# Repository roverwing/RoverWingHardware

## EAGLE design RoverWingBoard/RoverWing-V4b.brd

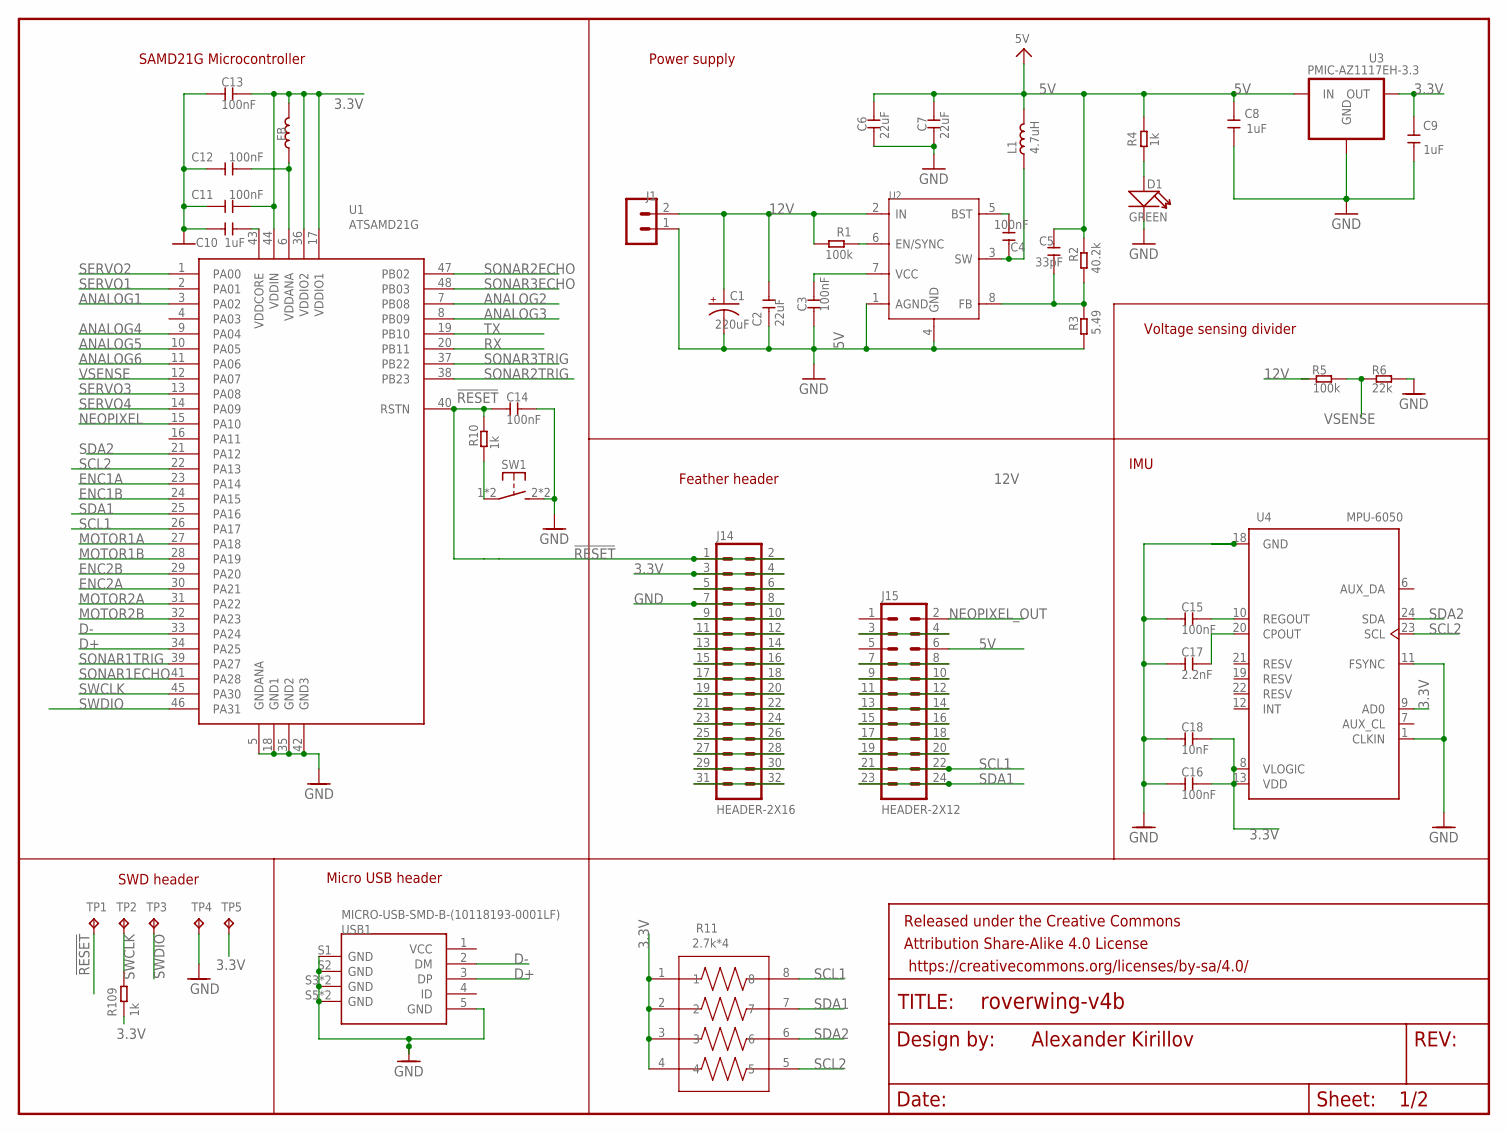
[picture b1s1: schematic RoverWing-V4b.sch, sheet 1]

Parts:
C1: 220uF; CAP-8X10.5
C2, C6, C7: 22uF; 0805
C3, C4, C11, C12, C13, C14, C15, C16: 100nF; 0805
C5: 33pF; 0805
C8, C9, C10: 1uF; 0805
C17: 2.2nF; 0805
C18: 10nF; 0805
D1: GREEN; LED-0805
FB: 330R-1500MA; 0805
FRAME2: FRAME-LETTERNO_PACKAGE; DUMMY
J1: HEADER-VH; B2P-VH
J14: HEADER-2X16; 2X16
J15: HEADER-2X12; 2X12
L1: 4.7uH; IND_TDK_7.1X6.5
R1, R5: 100k; 0805
R2: 40.2k; 0805
R3: 5.49; 0805
R4, R10, R109: 1k; 0805
R6: 22k; 0805
R11: 2.7k*4; 0603*4
SW1: SW-TACTILE-4.5X4.5_SMD; TL3305
TP1, TP2, TP3, TP4, TP5: TPTP15R; TP15R
U1: ATSAMD21G; TQFP-48-EDITED
U2: PMIC-MP2225; SOT-23-8
U3: PMIC-AZ1117EH-3.3; SOT223
U4: MPU-6050; QFN50P400X400X95-24N
USB1: MICRO-USB-SMD-B-(10118193-0001LF); MICRO-USB5+6P-SMD-0.65-B

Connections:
3.3V: C9.2, C11.2, C13.2, C16.2, C18.2, FB.2, J14.3, J14.4, R11.1, R11.2, R11.3, R11.4, R109.1, TP5.TP, U1.17 (VDDIO1), U1.36 (VDDIO2), U1.44 (VDDIN), U3.2 (OUT), U3.4 (OUT), U4.8 (VLOGIC), U4.9 (AD0), U4.13 (VDD); also elsewhere on the board
5V: C5.2, C6.2, C7.2, C8.2, J15.6, L1.2, R2.1, R4.2, U3.3 (IN); also elsewhere on the board
12V: C1.+, C2.2, J1.2, R1.2, R5.2, U2.2 (IN); also elsewhere on the board
!RESET: C14.1, J14.1, J14.2, R10.2, TP1.TP, U1.40 (RSTN)
ANALOG1: U1.3 (PA02); also elsewhere on the board
ANALOG2: U1.7 (PB08); also elsewhere on the board
ANALOG3: U1.8 (PB09); also elsewhere on the board
ANALOG4: U1.9 (PA04); also elsewhere on the board
ANALOG5: U1.10 (PA05); also elsewhere on the board
ANALOG6: U1.11 (PA06); also elsewhere on the board
BST: C4.1, U2.5 (BST)
D+: U1.34 (PA25), USB1.3 (DP)
D-: U1.33 (PA24), USB1.2 (DM)
ENC1A: U1.23 (PA14); also elsewhere on the board
ENC1B: U1.24 (PA15); also elsewhere on the board
ENC2A: U1.30 (PA21); also elsewhere on the board
ENC2B: U1.29 (PA20); also elsewhere on the board
FB: C5.1, R2.2, R3.1, U2.8 (FB)
GND: C1.-, C2.1, C3.1, C6.1, C7.1, C8.1, C9.1, C10.1, C11.1, C12.1, C13.1, C14.2, C15.1, C16.1, C17.1, C18.1, D1.-, J1.1, J14.7, J14.8, R3.2, R6.2, SW1.2 (S1), SW1.3 (S1), TP4.TP, U1.5 (GNDANA), U1.18 (GND1), U1.35 (GND2), U1.42 (GND3), U2.1 (AGND), U2.4 (GND), U3.1 (GND), U4.1 (CLKIN), U4.11 (FSYNC), U4.18 (GND), USB1.5 (GND), USB1.S1 (GND), USB1.S2 (GND), USB1.S3 (GND), USB1.S4 (GND), USB1.S5 (GND), USB1.S6 (GND); also elsewhere on the board
MOTOR1A: U1.27 (PA18); also elsewhere on the board
MOTOR1B: U1.28 (PA19); also elsewhere on the board
MOTOR2A: U1.31 (PA22); also elsewhere on the board
MOTOR2B: U1.32 (PA23); also elsewhere on the board
unnamed: C17.2, U4.20 (CPOUT)
unnamed: J15.3, J15.4
unnamed: C15.2, U4.10 (REGOUT)
unnamed: J15.7, J15.8
unnamed: R10.1, SW1.1, SW1.4 (P1)
unnamed: J15.9, J15.10
unnamed: C10.2, U1.43 (VDDCORE)
unnamed: J15.11, J15.12
unnamed: D1.+, R4.1
unnamed: J15.15, J15.16
unnamed: J15.13, J15.14
unnamed: R1.1, U2.6 (EN/SYNC)
unnamed: C3.2, U2.7 (VCC)
unnamed: J14.5, J14.6
unnamed: J15.17, J15.18
unnamed: J15.19, J15.20
unnamed: J14.9, J14.10
unnamed: J14.11, J14.12
unnamed: J14.13, J14.14
unnamed: J14.15, J14.16
unnamed: J14.17, J14.18
unnamed: J14.19, J14.20
unnamed: J14.21, J14.22
unnamed: J14.23, J14.24
unnamed: J14.25, J14.26
unnamed: J14.27, J14.28
unnamed: J14.29, J14.30
unnamed: J14.31, J14.32
NEOPIXEL: U1.15 (PA10); also elsewhere on the board
NEOPIXEL_OUT: J15.2; also elsewhere on the board
RX: U1.20 (PB11); also elsewhere on the board
SCL1: J15.21, J15.22, R11.8, U1.26 (PA17); also elsewhere on the board
SCL2: R11.5, U1.22 (PA13), U4.23 (SCL); also elsewhere on the board
SDA1: J15.23, J15.24, R11.7, U1.25 (PA16); also elsewhere on the board
SDA2: R11.6, U1.21 (PA12), U4.24 (SDA); also elsewhere on the board
SERVO1: U1.2 (PA01); also elsewhere on the board
SERVO2: U1.1 (PA00); also elsewhere on the board
SERVO3: U1.13 (PA08); also elsewhere on the board
SERVO4: U1.14 (PA09); also elsewhere on the board
SONAR1ECHO: U1.41 (PA28); also elsewhere on the board
SONAR1TRIG: U1.39 (PA27); also elsewhere on the board
SONAR2ECHO: U1.47 (PB02); also elsewhere on the board
SONAR2TRIG: U1.38 (PB23); also elsewhere on the board
SONAR3ECHO: U1.48 (PB03); also elsewhere on the board
SONAR3TRIG: U1.37 (PB22); also elsewhere on the board
SW: C4.2, L1.1, U2.3 (SW)
SWCLK: R109.2, TP2.TP, U1.45 (PA30)
SWDIO: TP3.TP, U1.46 (PA31)
TX: U1.19 (PB10); also elsewhere on the board
VDDANA: C12.2, FB.1, U1.6 (VDDANA)
VSENSE: R5.1, R6.1, U1.12 (PA07)

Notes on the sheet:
SWD header
Alexander Kirillov
SAMD21G Microcontroller
Micro USB header
Power supply
Feather header
IMU
Voltage sensing divider

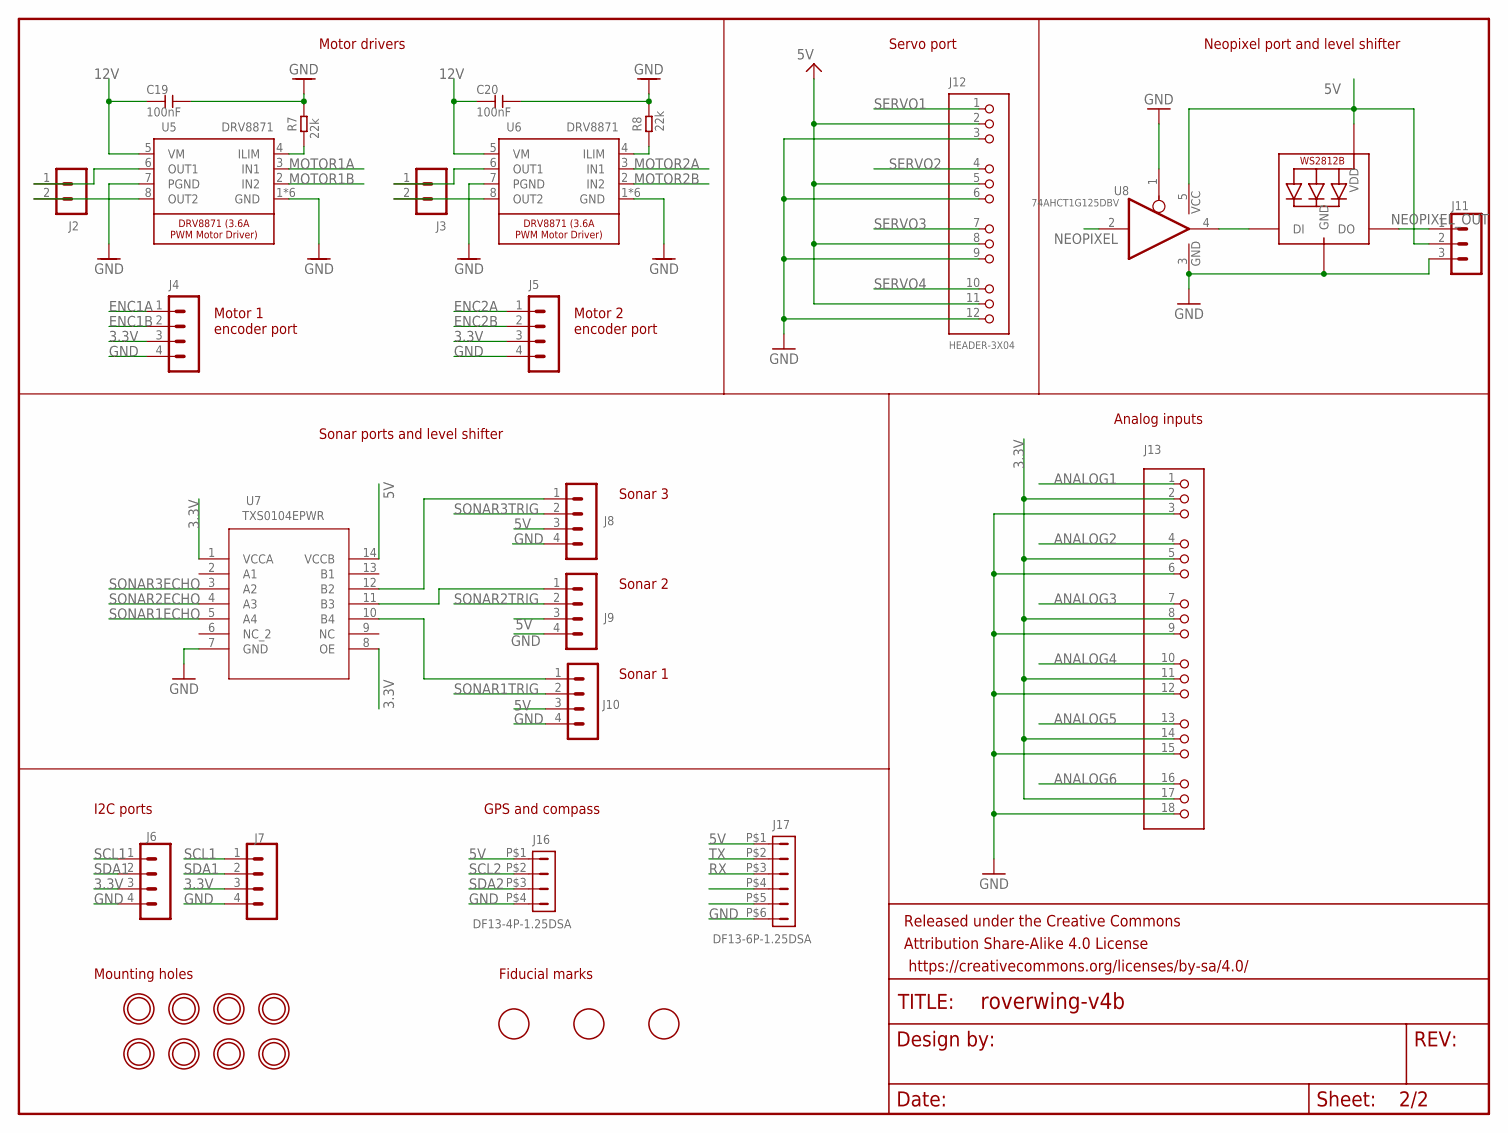
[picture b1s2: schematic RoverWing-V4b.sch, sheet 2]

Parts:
C19, C20: 100nF; 0805
FRAME1: FRAME-LETTERNO_PACKAGE; DUMMY
J2, J3: HEADER-VH; B2P-VH
J4, J5, J6, J7, J8, J9, J10: HEADER-PH-4P; B4B-PH-K
J11: HEADER-PH-3P; B3B-PH-K
J12: HEADER-3X04; 3X04
J13: HEADER-3X06"; 3X06
J16: DF13-4P-1.25DSA
J17: DF13-6P-1.25DSA
LED1: WS2812B3535; LED3535
R7, R8: 22k; 0805
U5, U6: DRV8871; HSOP8
U7: TXS0104EPWR; PW14
U8: 74AHCT1G125DBV; SOT23-5
U$3, U$4, U$14, U$15, U$24, U$25, U$26, U$27: MOUNTINGHOLE3.0_NPH; MOUNTINGHOLE_3.0_NPH
U$11, U$13, U$17: FIDUCIAL; FIDUCIAL_1MM

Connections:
3.3V: J4.3, J5.3, J6.3, J7.3, J13.2, J13.5, J13.8, J13.11, J13.14, J13.17, U7.1 (VCCA), U7.8 (OE); also elsewhere on the board
5V: J8.3, J9.3, J10.3, J11.2, J12.2, J12.5, J12.8, J12.11, J16.P$1 (1), J17.P$1 (1), LED1.2 (VDD), U7.14 (VCCB), U8.5 (VCC); also elsewhere on the board
12V: C19.1, C20.1, U5.5 (VM), U6.5 (VM); also elsewhere on the board
ANALOG1: J13.1; also elsewhere on the board
ANALOG2: J13.4; also elsewhere on the board
ANALOG3: J13.7; also elsewhere on the board
ANALOG4: J13.10; also elsewhere on the board
ANALOG5: J13.13; also elsewhere on the board
ANALOG6: J13.16; also elsewhere on the board
ENC1A: J4.1; also elsewhere on the board
ENC1B: J4.2; also elsewhere on the board
ENC2A: J5.1; also elsewhere on the board
ENC2B: J5.2; also elsewhere on the board
GND: C19.2, C20.2, J4.4, J5.4, J6.4, J7.4, J8.4, J9.4, J10.4, J11.3, J12.3, J12.6, J12.9, J12.12, J13.3, J13.6, J13.9, J13.12, J13.15, J13.18, J16.P$4 (4), J17.P$6 (6), LED1.4 (GND), R7.2, R8.2, U5.1 (GND), U5.7 (PGND), U5.GND, U5.P$1 (GND), U5.P$2 (GND), U5.P$3 (GND), U5.P$4 (GND), U6.1 (GND), U6.7 (PGND), U6.GND, U6.P$1 (GND), U6.P$2 (GND), U6.P$3 (GND), U6.P$4 (GND), U7.7 (GND), U8.1 (OE), U8.3 (GND); also elsewhere on the board
MOTOR1A: U5.3 (IN1); also elsewhere on the board
MOTOR1B: U5.2 (IN2); also elsewhere on the board
MOTOR2A: U6.3 (IN1); also elsewhere on the board
MOTOR2B: U6.2 (IN2); also elsewhere on the board
unnamed: J3.2, U6.8 (OUT2)
unnamed: J3.1, U6.6 (OUT1)
unnamed: J2.2, U5.8 (OUT2)
unnamed: J10.1, U7.10 (B4)
unnamed: J8.1, U7.12 (B2)
unnamed: J2.1, U5.6 (OUT1)
unnamed: R7.1, U5.4 (ILIM)
unnamed: R8.1, U6.4 (ILIM)
unnamed: J9.1, U7.11 (B3)
unnamed: LED1.1 (DI), U8.4 (O)
NEOPIXEL: U8.2 (I); also elsewhere on the board
NEOPIXEL_OUT: J11.1, LED1.3 (DO); also elsewhere on the board
RX: J17.P$3 (3); also elsewhere on the board
SCL1: J6.1, J7.1; also elsewhere on the board
SCL2: J16.P$2 (2); also elsewhere on the board
SDA1: J6.2, J7.2; also elsewhere on the board
SDA2: J16.P$3 (3); also elsewhere on the board
SERVO1: J12.1; also elsewhere on the board
SERVO2: J12.4; also elsewhere on the board
SERVO3: J12.7; also elsewhere on the board
SERVO4: J12.10; also elsewhere on the board
SONAR1ECHO: U7.5 (A4); also elsewhere on the board
SONAR1TRIG: J10.2; also elsewhere on the board
SONAR2ECHO: U7.4 (A3); also elsewhere on the board
SONAR2TRIG: J9.2; also elsewhere on the board
SONAR3ECHO: U7.3 (A2); also elsewhere on the board
SONAR3TRIG: J8.2; also elsewhere on the board
TX: J17.P$2 (2); also elsewhere on the board

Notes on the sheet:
Motor drivers
Motor 2 encoder port
Motor 1 encoder port
Sonar ports and level shifter
Analog inputs
Neopixel port and level shifter
Servo port
Sonar 3
Sonar 2
Sonar 1
Mounting holes
Fiducial marks
I2C ports
GPS and compass

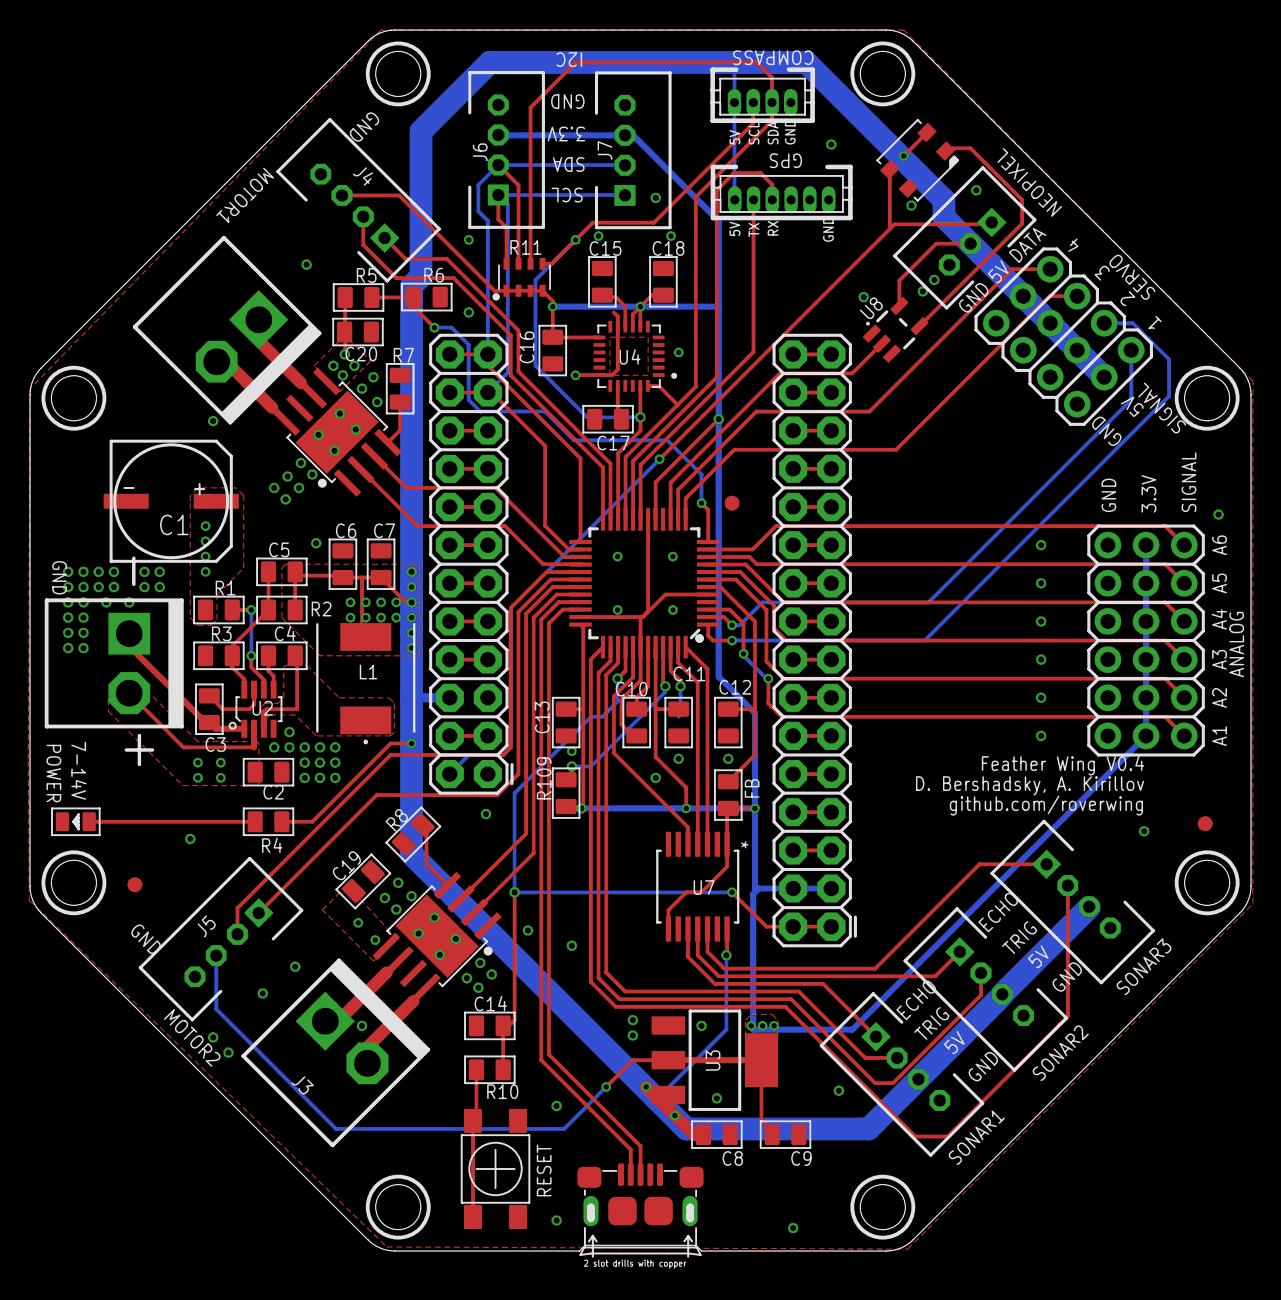
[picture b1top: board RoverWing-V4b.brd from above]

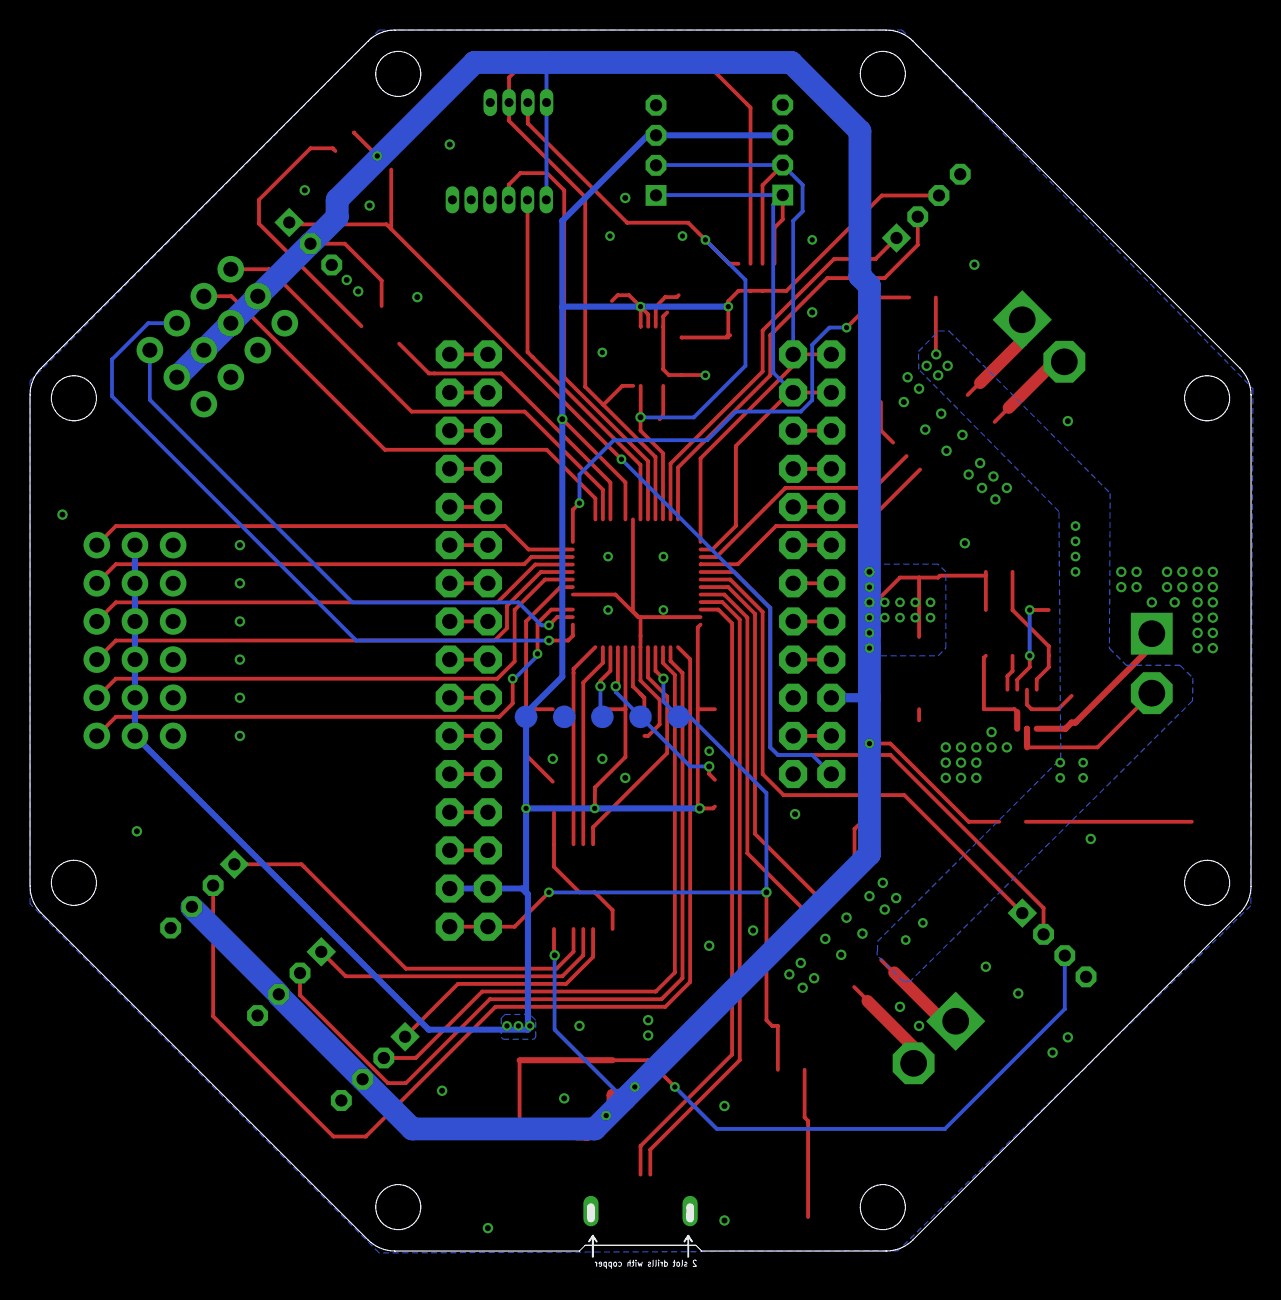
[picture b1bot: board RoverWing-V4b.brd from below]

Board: 2 copper layers, 81.3 x 81.3 mm, 80 parts (5 on the bottom side), 84 nets.

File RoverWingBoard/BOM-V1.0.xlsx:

Parts | Qty | Value | Description | Part Num | Package | Mfg Name | Vendor | Vendor Part Num | Min quantity | Unit price | URL | Extended price
C1 | 1 | 220uF | CAP ALUM 220uF 20% 35V SMD | CK1V221MCRF10 | CAP-8X10.5 | Semtech | LCSC | C263948 | 5 | 7.2499999999999995E-2 | https://lcsc.com/product-detail/Others_Semtech-CKF1V221M0810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 | 7.2499999999999995E-2
C17 | 1 | 2.2nF | CAP CER 2.2NF 50V | C2012X7R1H222KT000N | 0805 | TDK | LCSC | C76647 | 50 | 1.52E-2 | https://lcsc.com/product-detail/Multilayer-Ceramic-Capacitor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 | 1.52E-2
C18 | 1 | 10nF | CAP CER 10NF 100V | CL21B103KCANNNC | 0805 | Samsung Electro-Mechanics | LCSC | C18741 | 50 | 1.35E-2 | https://lcsc.com/product-detail/Multilayer-Ceramic-Capacitor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 | 1.35E-2
C2, C6, C7 | 3 | 22uF | CAP CER 22uF 25V X5R | CL21A226MAQNNNE | 0805 | Samsung Electro-Mechanics | LCSC | C45783 | 5 | 0.12239999999999999 | https://lcsc.com/product-detail/Multilayer-Ceramic-Capacitor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 | 0.36719999999999997
C3, C4, C11, C12, C13, C14, C15, C16, C19, C20 | 10 | 100nF | CAP CER 0.1UF 50V | 0805B104M500NT | 0805 | Guangdong Fenghua Advanced Tech | LCSC | C286511 | 50 | 1.6899999999999998E-2 | https://lcsc.com/product-detail/Others_Guangdong-Fenghua-Adv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 | 0.16899999999999998
C5 | 1 | 33pF | CAP CER 33pF 50V | CL21C330JBANNNC | 0805 | Samsung Electro-Mechanics | LCSC | C1814 | 50 | 1.23E-2 | https://lcsc.com/product-detail/Multilayer-Ceramic-Capacitor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 | 1.23E-2
C8, C9, C10 | 3 | 1uF | CAP CER 1uF 25V | 0805B105K250AT | 0805 | Guangdong Fenghua Advanced Tech | LCSC | C111769 | 20 | 2.0299999999999999E-2 | https://lcsc.com/product-detail/Multilayer-Ceramic-Capacitor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 | 6.0899999999999996E-2
D1 | 1 | GREEN | Light Emitting Diodes (LED) Green 567.5~576.5nm 18~71mcd@20mA Top View 0805 RoHS | LTST-C170KGKT | LED-0805 | Lite-On | LCSC | C98221 | 20 | 2.76E-2 | https://lcsc.com/product-detail/Light-Emitting-Diodes-LED_LT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 | 2.76E-2
FB | 1 | 330R-1500MA | FERRITE BEAD 330 OHM 0805 1LN | BLM21PG331SN1D | 0805 | Murata Electronics | LCSC | C74764 | 20 | 3.5099999999999999E-2 | https://lcsc.com/product-detail/Ferrite-Beads-And-Chips_muRa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 | 3.5099999999999999E-2
J1, J2, J3 | 3 | HEADER-VH | CONN HEADER VH TOP 2POS 3.96MM | B2P-VH(LF)(SN) | B2P-VH | JST Sales America | LCSC | C160315 | 5 | 6.6799999999999998E-2 | * | 0.20039999999999999
J11 | 1 | HEADER-PH-3P | CONN HEADER PH TOP 3POS 2MM | B3B-PH-K-S(LF)(SN) | B3B-PH-K | JST Sales America | LCSC | C131339 | 5 | 9.9699999999999997E-2 | https://lcsc.com/product-detail/PCB-Connectors-Headers-Male-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 | 9.9699999999999997E-2
J12 | 1 | HEADER-3X04 | * | * | 3X04 | * | * | * | * | * | *
J13 | 1 | HEADER-3X06 | * | * | 3X06 | * | * | * | * | * | *
J14 | 1 | HEADER-2X16 | FEMALE HEADER 2*16 2.54MM | DS1023-2*16SF11 | 2X16 | CONNFLY Elec | LCSC | C132130 | 1 | 0.1454 | https://lcsc.com/product-detail/Female-Header_DS1023-2-16SF1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 | 0.1454
J15 | 1 | HEADER-2X12 | FEMALE HEADER 2*12 2.54MM | DS1023-2*12SF11 | 2X12 | CONNFLY Elec | LCSC | C92265 | 1 | 0.1201 | https://lcsc.com/product-detail/Female-Header_2-54Female-hea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 | 0.1201
J16 | 1 | DF13-4P-1.25DSA | CONN HEADER DF13 4POS 1.25MM | DF13-4P-1.25DSA | DF13-4P-1.25DSA | Hirose | LCSC | C202091 | 1 | 0.26550000000000001 | https://lcsc.com/product-detail/Connectors_Hirose_DF13-4P-1-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 | 0.26550000000000001
J17 | 1 | DF13-6P-1.25DSA | CONN HEADER DF13 6POS 1.25MM | DF13-6P-1.25DSA | DF13-6P-1.25DSA | Hirose | Digikey | H2195-ND | 1 | 0.33 | https://www.digikey.com/product-detail/en/hirose-electric-co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 | 0.33
J4, J5, J6, J7, J8, J9, J10 | 7 | HEADER-PH-4P | CONN HEADER PH TOP 4POS 2MM | B4B-PH-K-S(LF)(SN) | B4B-PH-K | JST Sales America | LCSC | C160257 | 10 | 5.91E-2 | https://lcsc.com/product-detail/Wire-To-Board-Wire-To-Wire-C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 | 0.41370000000000001
L1 | 1 | 4.7uH | Power Inductors 4.7uH Â±20% 5.6A | SPM6530T-4R7M | IND_TDK_7.1X6.5 | TDK | LCSC | C76857 | 10 | 0.1082 | https://lcsc.com/product-detail/Power-Inductors_TDK_SPM6530T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 | 0.1082
LED1 | 1 | WS2812B3535 | SMART LED, 3.5MM SMD | WS2812B-3535 | LED3535 | Worldsemi | LCSC | C114583 | 5 | 0.1145 | https://lcsc.com/product-detail/Light-Emitting-Diodes-LED_35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 | 0.1145
R1, R5 | 2 | 100k | RES SMD 100K OHM 1% | RC0805FR-07100KL | 0805 | YAGEO | LCSC | C96346 | 50 | 5.4000000000000003E-3 | https://lcsc.com/product-detail/Chip-Resistor-Surface-Mount_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 | 1.0800000000000001E-2
R11 | 1 | 2.7k*4 | Resistor Networks & Arrays 2.7KOhms Â±5% 1/16W 0603_x4 | RTA03-4D272JTP | 0603*4 | RALEC | LCSC | C102660 | 50 | 8.6999999999999994E-3 | https://lcsc.com/product-detail/Resistor-Networks-Arrays_2-7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 | 8.6999999999999994E-3
R2 | 1 | 40.2k | RES SMD 40.2KOhms ±1% 1/8W 0805 RoHS | RC0805FR-0740K2L | 0805 | YAGEO | LCSC | C273827 | 100 | 2.3999999999999998E-3 | https://lcsc.com/product-detail/Others_YAGEO-RC0805FR-0740K2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 | 2.3999999999999998E-3
R3 | 1 | 5.49 | RES SMD 5.49KOhms ±1% 1/8W 0805 RoHS | RC0805FR-075K49L | 0805 | YAGEO | LCSC | C273977 | 50 | 3.8E-3 | https://lcsc.com/product-detail/Others_YAGEO-RC0805FR-075K49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 | 3.8E-3
R4, R10, R109 | 3 | 1k | RES SMD 1K OHMs Â±5% 1/8W | RC0805JR-071KL | 0805 | YAGEO | LCSC | C100046 | 50 | 2.7000000000000001E-3 | https://lcsc.com/product-detail/Chip-Resistor-Surface-Mount_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 | 8.0999999999999996E-3
R6, R7, R8 | 3 | 22k | RES SMD 22KOhms Â±1% | RC0805FR-0722KL | 0805 | YAGEO | LCSC | C114565 | 50 | 4.3E-3 | https://lcsc.com/product-detail/Chip-Resistor-Surface-Mount_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 | 1.29E-2
SW1 | 1 | SW-TACTILE-4.5X4.5_SMD | Tactile Switches SPST 4.50mm x 4.50mm 0.90mm 50mA @ 12VDC SMD RoHS | TSA453G38-250 | TL3305 | BRIGHT | LCSC | C294494 | 20 | 2.5399999999999999E-2 | https://lcsc.com/product-detail/Tactile-Switches_BRIGHT-TSA4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 | 2.5399999999999999E-2
U1 | 1 | ATSAMD21G | IC MCU 32BIT 256KB FLASH 48TQFP | ATSAMD21G18A-AU | TQFP-48-EDITED | Microchip Technology | Digikey | ATSAMD21G18A-AU-ND | 1 | 3.22 | https://www.digikey.com/product-detail/en/microchip-technolo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 | 3.22
U2 | 1 | PMIC-MP2225 | DC-DC Converters Step-Down Adjustable 1 4.5V 18V 0.6V 17V 5A TSOT-23-8Â | MP2225GJ-Z | SOT-23-8 | Monolithic Power Systems | LCSC | C133066 | 10 | 0.32140000000000002 | https://lcsc.com/product-detail/DC-DC-Converters_MPS_MP2225G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 | 0.32140000000000002
U3 | 1 | AZ1117EH-3.3 | Low Dropout Regulators(LDO) Positive Fixed 1.3V @ 1A 13V 3.3V 1AÂ | AZ1117EH-3.3TRG1 | SOT223 | Diodes Inc | LCSC | C108494 | 5 | 8.1299999999999997E-2 | https://lcsc.com/product-detail/Low-Dropout-Regulators-LDO_D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 | 8.1299999999999997E-2
U4 | 1 | MPU-6050 | IMU ACCEL/GYRO 3-AXIS I2C 24QFN | MPU-6050 | QFN50P400X400X95-24N | TDK InvenSense | LCSC | C24112 | 1 | 2.8835000000000002 | https://lcsc.com/product-detail/Attitude-Sensors_TDK-InvenSe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 | 2.8835000000000002
U5, U6 | 2 | DRV8871 | Motor Drivers SO-8 RoHS | DRV8871DDAR | HSOP8 | Texas Instruments | LCSC | C75864 | 1 | 1.7250000000000001 | https://lcsc.com/product-detail/Motor-Drivers_TI_DRV8871DDAR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 | 3.45
U7 | 1 | TXS0104EPWR | Level Translators, Shifters TSSOP-14 RoHS | TXS0104EPWR | PW14 | Texas Instruments | LCSC | C44955 | 1 | 0.69340000000000002 | https://lcsc.com/product-detail/Interface-ICs_TI_TXS0104EPWR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 | 0.69340000000000002
U8 | 1 | 74AHCT1G125DBV | 74 Series Buffer, Non-Inverting 4.5V ~ 5.5V SOT-23-5 RoHS | SN74AHCT1G125DBVR | SOT23-5 | Texas Instruments | LCSC | C7484 | 5 | 0.12809999999999999 | https://lcsc.com/product-detail/74-Series_TI_SN74AHCT1G125DB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 | 0.12809999999999999
USB1 | 1 | MICRO-USB-SMD-B-(10118193-0001LF) | CONN USB MICRO B RECPT SMT R/A | 10118193-0001LF | MICRO-USB5+6P-SMD-0.65-B | Amphenol ICC | LCSC | C132562 | 1 | 0.24 | https://lcsc.com/product-detail/USB-Connectors_Amphenol_1011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 | 0.24
Total price

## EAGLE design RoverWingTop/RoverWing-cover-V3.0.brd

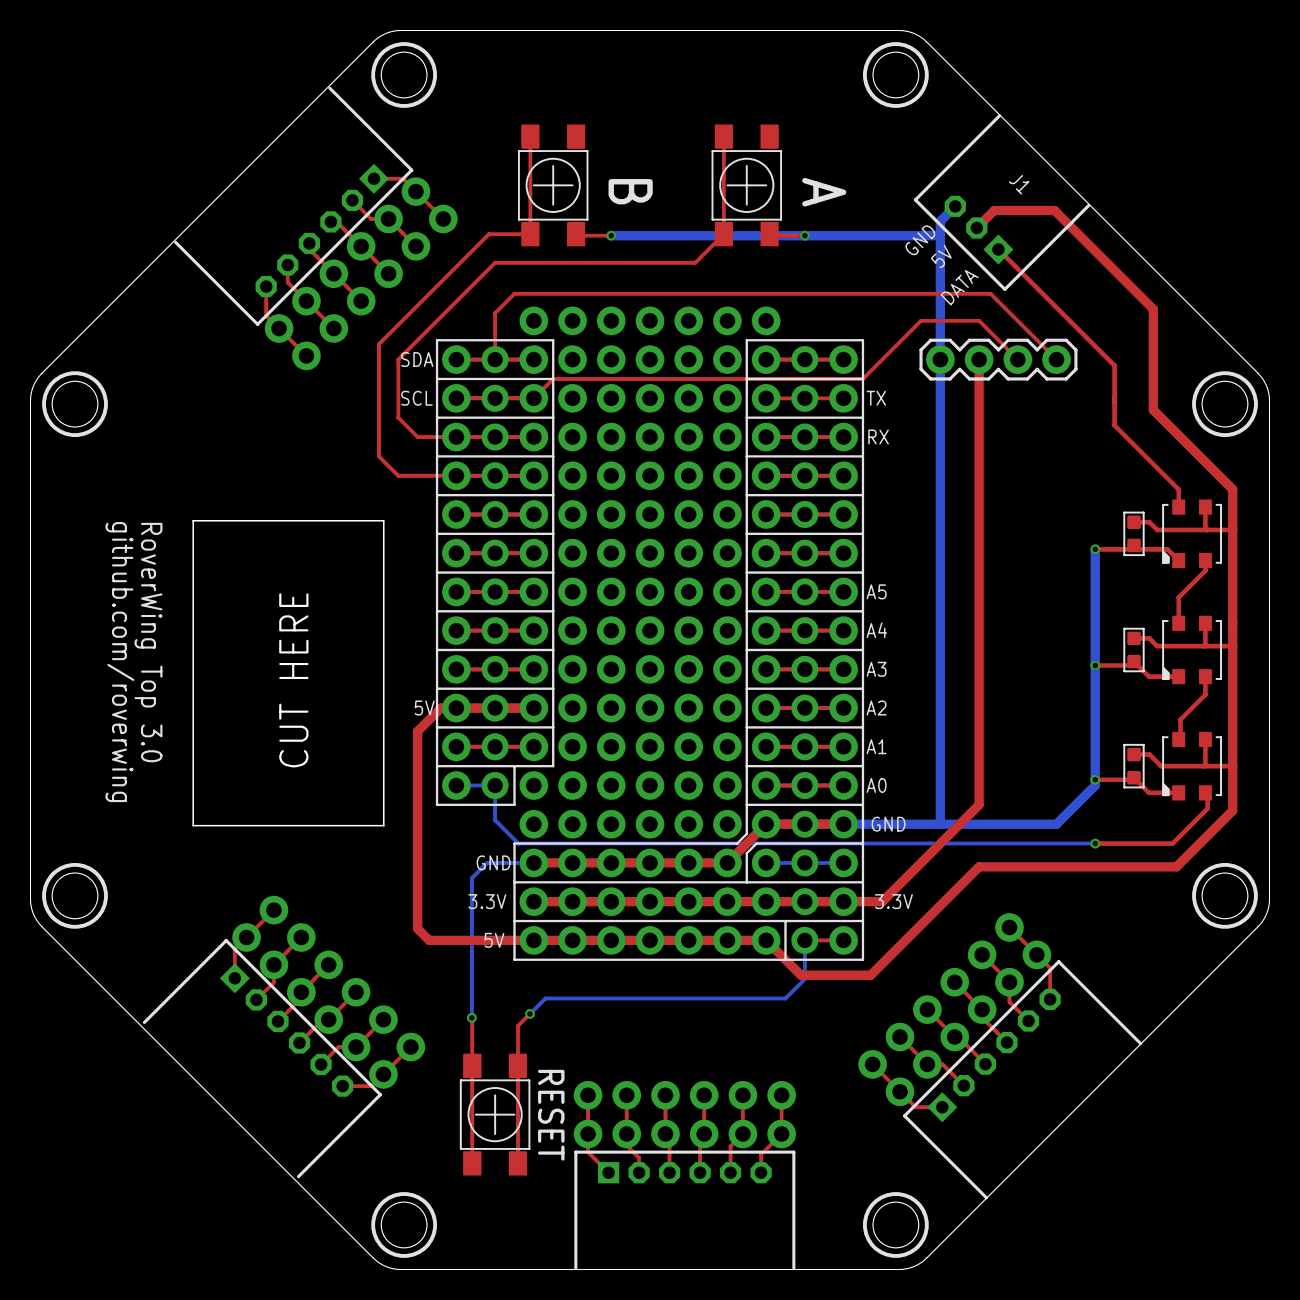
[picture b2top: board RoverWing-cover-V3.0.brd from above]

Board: 2 copper layers, 81.3 x 81.3 mm, 52 parts (0 on the bottom side), 55 nets.

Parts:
C1, C2, C3: 0.1uF; 0603
FRAME2: FRAME-LETTERNO_PACKAGE; DUMMY
J1: HEADER-PH-3PSIDEENTRY; S3B-PH-K
J2: 1X04
J3: 1X12_NO_SILK
J4: 1X16_NO_SILK
J5, J10, J13, J17: HEADER-PH-6PSIDEENTRY; S6B-PH-K
J6, J7, J8, J9, J11, J12, J14, J15: 1X06_NO_SILK
J16: FEATHERWING_NODIM; FEATHERWING_DIM
J101, J102, J103, J104, J105, J106, J107, J108, J109, J110, J111, J112, J113, J114, J115, J116, J117: 1X07_NO_SILK
LED1, LED2, LED3: LED3535
S1, S2, S3: SW-TACTILE-4.5X4.5_SMD; TL3305
U$3, U$4, U$14, U$15, U$24, U$25, U$26, U$27: MOUNTINGHOLE3.0_NPH; MOUNTINGHOLE_3.0_NPH

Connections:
3.3V: J2.2, J4.15, J16.2, J116.1, J116.2, J116.3, J116.4, J116.5, J116.6, J116.7
5V: C1.2, C2.2, C3.2, J1.2, J3.3, J16.26, J111.1, J117.1, J117.2, J117.3, J117.4, J117.5, J117.6, J117.7, LED1.3, LED2.3, LED3.3
A0: J4.12, J16.5, J113.7
A1: J4.11, J16.6, J112.7
A2: J4.10, J16.7, J111.7
A3: J4.9, J16.8, J110.7
A4: J4.8, J16.9, J109.7
A5: J4.7, J16.10, J108.7
AREF: J4.14, J16.3, J115.7
D05: J3.10, J16.19, J104.1, S2.1, S2.4
D06: J3.9, J16.20, J105.1, S3.1, S3.4
D09: J3.8, J16.21, J106.1
D10: J3.7, J16.22, J107.1
D11: J3.6, J16.23, J108.1
D12: J3.5, J16.24, J109.1
D13: J3.4, J16.25, J110.1
EXTRA: J4.1, J16.16, J102.7
FEATHER_RESET: J4.16, J16.1, S1.1, S1.4
GND: C1.1, C2.1, C3.1, J1.3, J2.1, J4.13, J16.4, J114.7, J115.1, J115.2, J115.3, J115.4, J115.5, J115.6, LED1.1, LED2.1, LED3.1, S1.2, S1.3, S2.2, S2.3, S3.2, S3.3
MISO: J4.4, J16.13, J105.7
MOSI: J4.5, J16.12, J106.7
unnamed: LED2.4, LED3.2
unnamed: J5.1, J7.1, J8.1
unnamed: LED1.4, LED2.2
unnamed: J5.2, J7.2, J8.2
unnamed: J5.3, J7.3, J8.3
unnamed: J5.4, J7.4, J8.4
unnamed: J5.5, J7.5, J8.5
unnamed: J5.6, J7.6, J8.6
unnamed: J6.1, J9.1, J10.1
unnamed: J6.2, J9.2, J10.2
unnamed: J6.3, J9.3, J10.3
unnamed: J6.4, J9.4, J10.4
unnamed: J6.5, J9.5, J10.5
unnamed: J6.6, J9.6, J10.6
unnamed: J11.1, J12.1, J13.1
unnamed: J11.2, J12.2, J13.2
unnamed: J11.3, J12.3, J13.3
unnamed: J11.4, J12.4, J13.4
unnamed: J11.5, J12.5, J13.5
unnamed: J11.6, J12.6, J13.6
unnamed: J14.1, J15.1, J17.1
unnamed: J14.2, J15.2, J17.2
unnamed: J14.3, J15.3, J17.3
unnamed: J14.4, J15.4, J17.4
unnamed: J14.5, J15.5, J17.5
unnamed: J14.6, J15.6, J17.6
unnamed: J3.2, J16.27, J112.1
NEOPIXEL: J3.1, J16.28, LED1.2
NEOPIXEL_OUT: J1.1, LED3.4
RX: J4.3, J16.14, J104.7
SCK: J4.6, J16.11, J107.7
SCL: J2.3, J3.11, J16.18, J103.1
SDA: J2.4, J3.12, J16.17, J102.1
TX: J4.2, J16.15, J103.7

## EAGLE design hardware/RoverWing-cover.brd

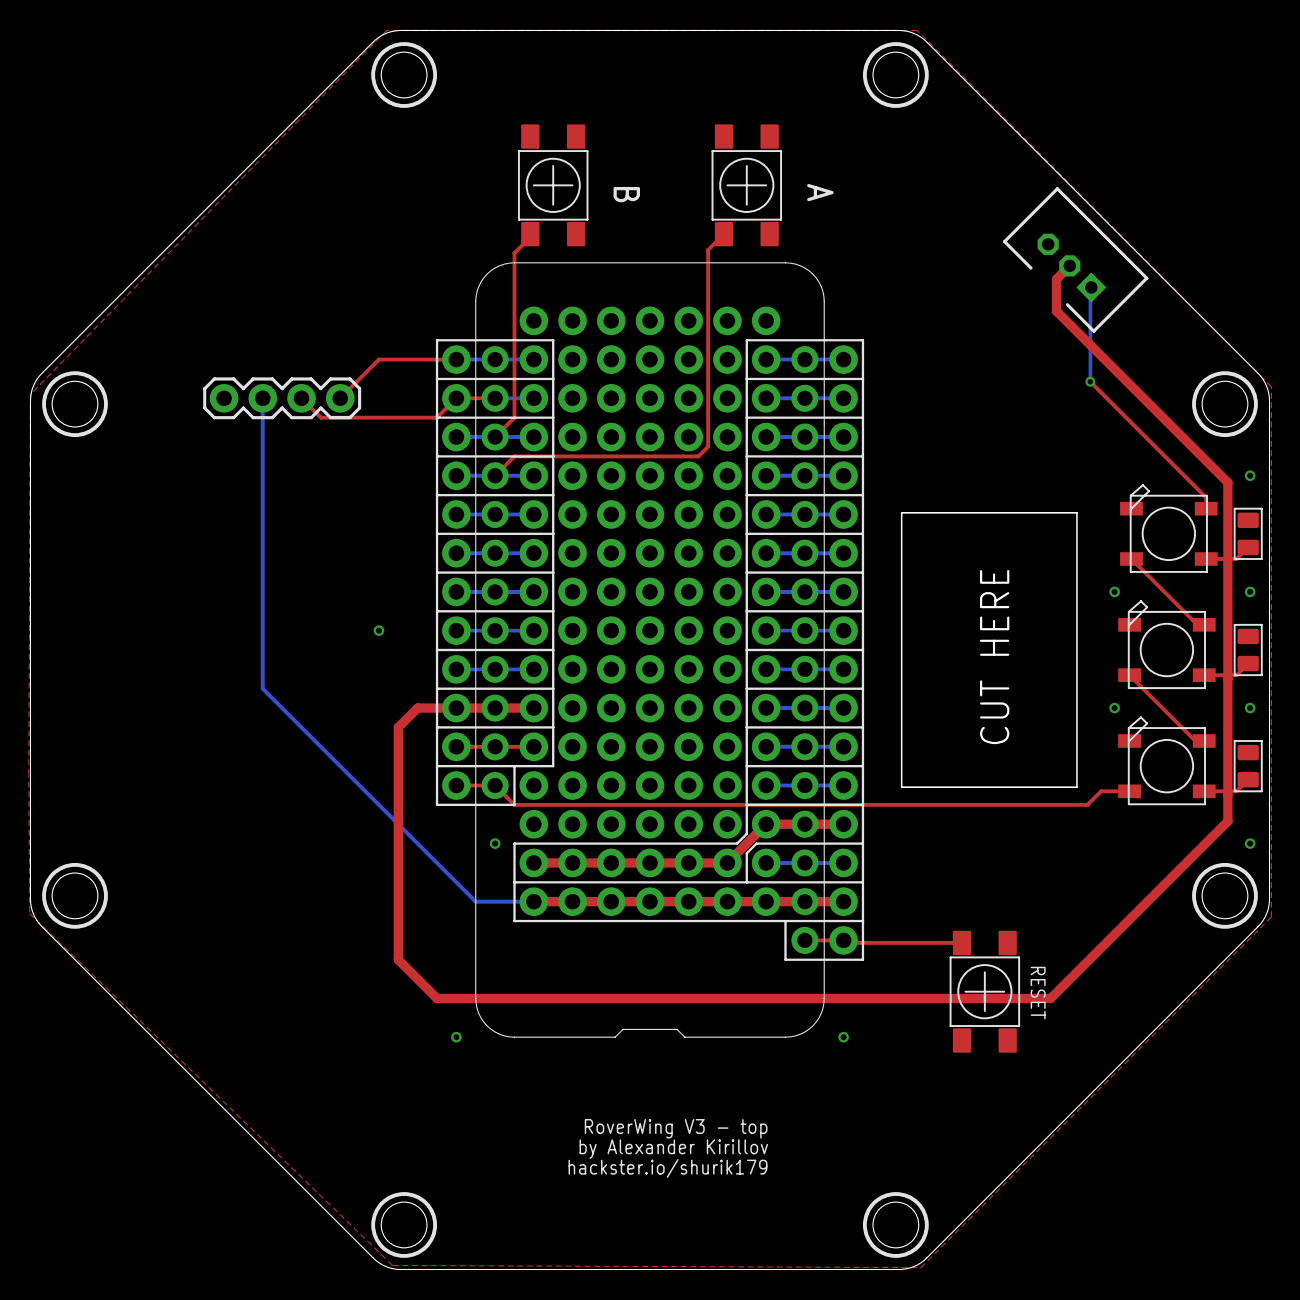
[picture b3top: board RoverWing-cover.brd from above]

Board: 2 copper layers, 81.3 x 81.3 mm, 39 parts (0 on the bottom side), 31 nets.

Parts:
C1, C2, C3: 0.1uF; C0805
FRAME2: FRAME-LETTERNO_PACKAGE; DUMMY
J1: HEADER-PH-3P; B3B-PH-K
J2: 1X04
J3: 1X12_NO_SILK
J4: 1X16_NO_SILK
J5, J6, J7, J9, J10, J11, J12, J13, J15, J17, J18, J19, J20, J21, J22, J23: 1X07_NO_SILK
J16: FEATHERWING_NODIM; FEATHERWING_DIM
LED1, LED2, LED3: WS2812B5050; WS2812B
S1, S2, S3: SW-TACTILE-4.5X4.5_SMD; TL3305
U$3, U$4, U$14, U$15, U$24, U$25, U$26, U$27: MOUNTINGHOLE3.0_NPH; MOUNTINGHOLE_3.0_NPH

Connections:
3.3V: J2.2, J4.15, J16.2, J22.1, J22.2, J22.3, J22.4, J22.5, J22.6, J22.7
5V: C1.2, C2.2, C3.2, J1.2, J3.3, J16.26, J17.1, LED1.1-VDD, LED2.1-VDD, LED3.1-VDD
A0: J4.12, J16.5, J19.7
A1: J4.11, J16.6, J18.7
A2: J4.10, J16.7, J17.7
A3: J4.9, J15.7, J16.8
A4: J4.8, J13.7, J16.9
A5: J4.7, J12.7, J16.10
AREF: J4.14, J16.3, J21.7
D05: J3.10, J7.1, J16.19, S3.1, S3.4
D06: J3.9, J9.1, J16.20, S2.1, S2.4
D09: J3.8, J10.1, J16.21
D10: J3.7, J11.1, J16.22
D11: J3.6, J12.1, J16.23
D12: J3.5, J13.1, J16.24
D13: J3.4, J15.1, J16.25
EXTRA: J4.1, J5.7, J16.16
FEATHER_RESET: J4.16, J16.1, S1.2, S1.3
GND: C1.1, C2.1, C3.1, J1.3, J2.1, J4.13, J16.4, J20.7, J21.1, J21.2, J21.3, J21.4, J21.5, J21.6, LED1.3-GND, LED2.3-GND, LED3.3-GND, S1.1, S1.4, S2.2, S2.3, S3.2, S3.3
MISO: J4.4, J9.7, J16.13
MOSI: J4.5, J10.7, J16.12
unnamed: LED2.2-DOUT, LED3.4-DIN
unnamed: LED1.2-DOUT, LED2.4-DIN
unnamed: J3.2, J16.27, J18.1
NEOPIXEL_IN: J3.1, J16.28, LED1.4-DIN
NEOPIXEL_OUT: J1.1, LED3.2-DOUT
RX: J4.3, J7.7, J16.14
SCK: J4.6, J11.7, J16.11
SCL: J2.3, J3.11, J6.1, J16.18
SDA: J2.4, J3.12, J5.1, J16.17
TX: J4.2, J6.7, J16.15

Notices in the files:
parts and their libraries:
RoverWing: Released under the Creative Commons
RoverWing: https://creativecommons.org/licenses/by-sa/4.0
SparkFun-Aesthetics: Licensing: Creative Commons ShareAlike 4.0 International - https://creativecommons.org/licenses/by-sa/4.0
